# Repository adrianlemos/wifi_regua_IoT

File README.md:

## Selecione o Idioma: | Português | [Inglês](./README_en.md) | [Espanhol](./README_es.md) |

### Geral
Este é um projeto Open Source/Open Hardware com a intenção de retribuir um pouco com a comunidade por tudo o que eu já consumi de informação.

### Idéia para o Projeto.
Como noventa porcento dos projetos são feitos por conta de preguiça, eu possuia uma regua de energia e queria automatizar a Ligação ON/OFF dela. com isso eu possuia uma regua de energia igual ao da imagem

### Hardware
Itens Necessários para a montagem.

01 unidade - Caixa Régua de Tensão [Marca: Patola Modelo: PB-560/6](http://www.patola.com.br/index.php?route=product/product&product_id=66&search=PB+560%2F6)

### Software

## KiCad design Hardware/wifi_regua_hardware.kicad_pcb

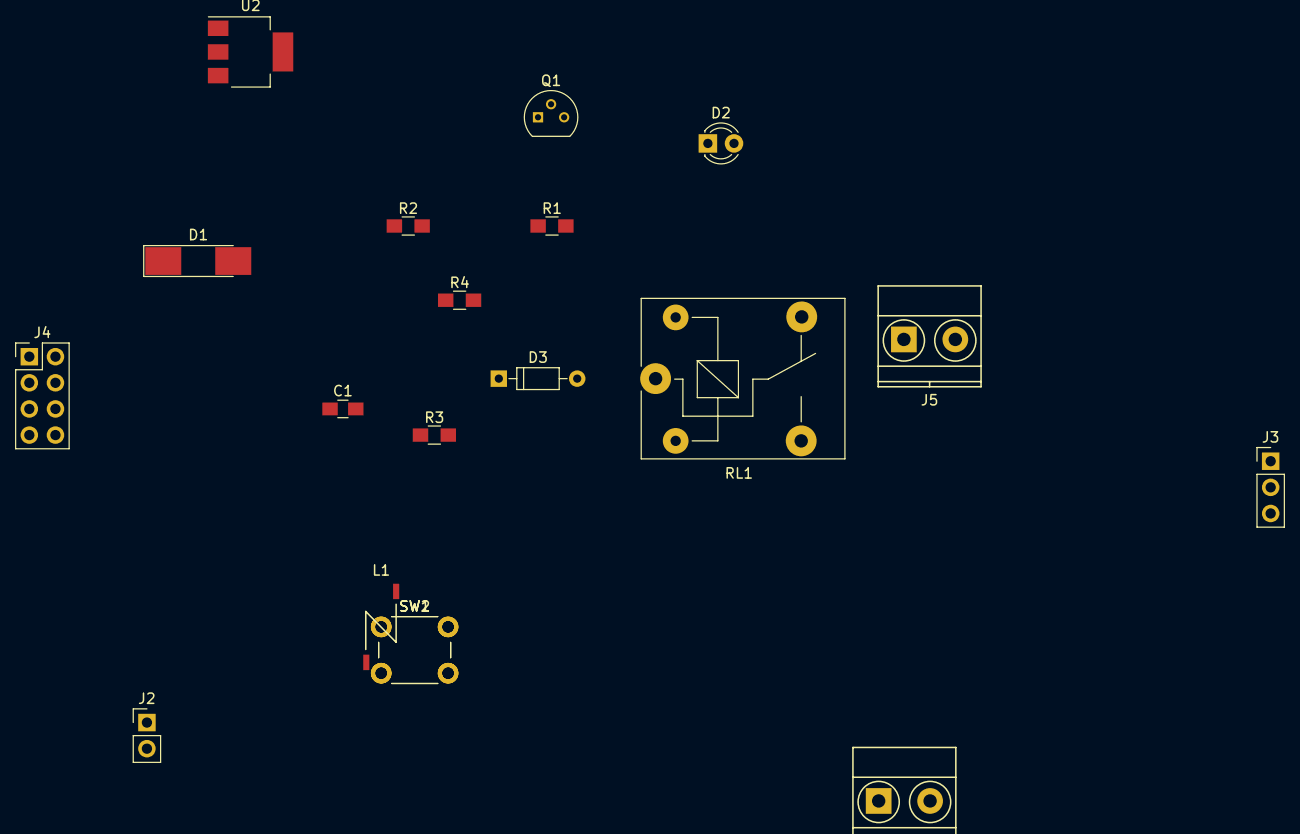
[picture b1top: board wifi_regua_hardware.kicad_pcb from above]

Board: 2 copper layers, 19 parts (0 on the bottom side), 14 nets, no tracks yet.

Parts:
C1: C_Small; C_0805_HandSoldering
D1: D_Zener; D_MELF_Handsoldering
D2: LED; LED_D3.0mm
D3: 1N4148; D_DO-35_SOD27_P7.62mm_Horizontal
J1, J5: Screw_Terminal_1x02; TerminalBlock_Pheonix_MKDS1.5-2pol
J2: CONN_01X02; Pin_Header_Straight_1x02_Pitch2.54mm
J3: CONN_01X03; Pin_Header_Straight_1x03_Pitch2.54mm
J4: CONN_02X04; Pin_Header_Straight_2x04_Pitch2.54mm
L1: L; Neosid_Air-Coil_SML_1turn_HDM0131A
Q1: BC548; TO-92_Molded_Narrow
R1, R2, R3: R_Small; R_0805_HandSoldering
R4: R; R_0805_HandSoldering
RL1: FINDER-36.11.4001; Relay_SPDT_SANYOU_SRD_Series_Form_C
SW1, SW2: SW_Push_Dual; SW_PUSH_6mm
U2: LM1117-3.3; SOT-223

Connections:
+3V3: C1.1, D1.1, J4.8, L1.2, R1.2, R2.1
+5V: D3.1, U2.3
AC_2: J1.2, J5.1
GND: C1.2, D1.2, J2.2, J3.3, J4.1, Q1.3, SW1.1, SW2.1, U2.1
unnamed: D2.1, D3.2, Q1.1
unnamed: D2.2, R4.1
unnamed: J4.4, R2.2
unnamed: L1.1, U2.2, U2.4
unnamed: Q1.2, R3.1
Prog_Mod: J2.1, J4.5, R1.1, SW2.2
RX: J3.2, J4.7
Relay_Activation: J4.3, R3.2
Reset: J4.6, SW1.2
TX: J3.1, J4.2

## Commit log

2017-03-26 arquivo inicial do software
2017-03-26 commit inicial do hardware
2017-03-27 Update README.md
    atualização do Read-me
2017-04-25 Mudanças no Hardware com a criação do Schematico de maneira que já é possivel reproduzi-lo
2022-04-07 Alteração do Readme
2022-04-07 no message
